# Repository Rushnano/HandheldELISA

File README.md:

# Handheld Point of Care ELISA
Electro Bio Chemical Potentiostat Testing Device for ELISA Test Cards
# 
  We are seeking contributors for creation of diversified testing device allowing consumable test cards capable of ELISA tests.

  The test cards may include protiens, enzymes, antibodies that allow capillary mixing and filtration with analyte so as to cause    a reaction in the working sensing zone. The working zone shall have excitation, sense and reference potentiostat electrodes for electronically sensing the the analyte/antibody reactions. The test card should also include near field radio frequency indentification for serial number, card test type, and date code.
  
  Added test card connections may also be included for electrophoresis as these electrodes may be required for fluidic movement. Hopefully we can limit these extra connections to the number of 8.

  The testing devices shall have circuitry and software included to perform a range of potentiostat test methods for a set of 2 electrode circuits. One set of electrodes will be sensing the real analyte response signal and the other set of electrodes will be used for relative reactions as reference. Potentiostat functions should be able to perform high resolution high sensitivity testing using static settings like many glucose meters to more complex features like differential pulse voltammetry.

  The testing device should be capable of near field radio frequency indentification reading for serial number, card test type, and date code to be used for test configuration parameters for that particular sensor card.

  App supported host connection using bluetooth should be included for intermediary cloud data services and display.

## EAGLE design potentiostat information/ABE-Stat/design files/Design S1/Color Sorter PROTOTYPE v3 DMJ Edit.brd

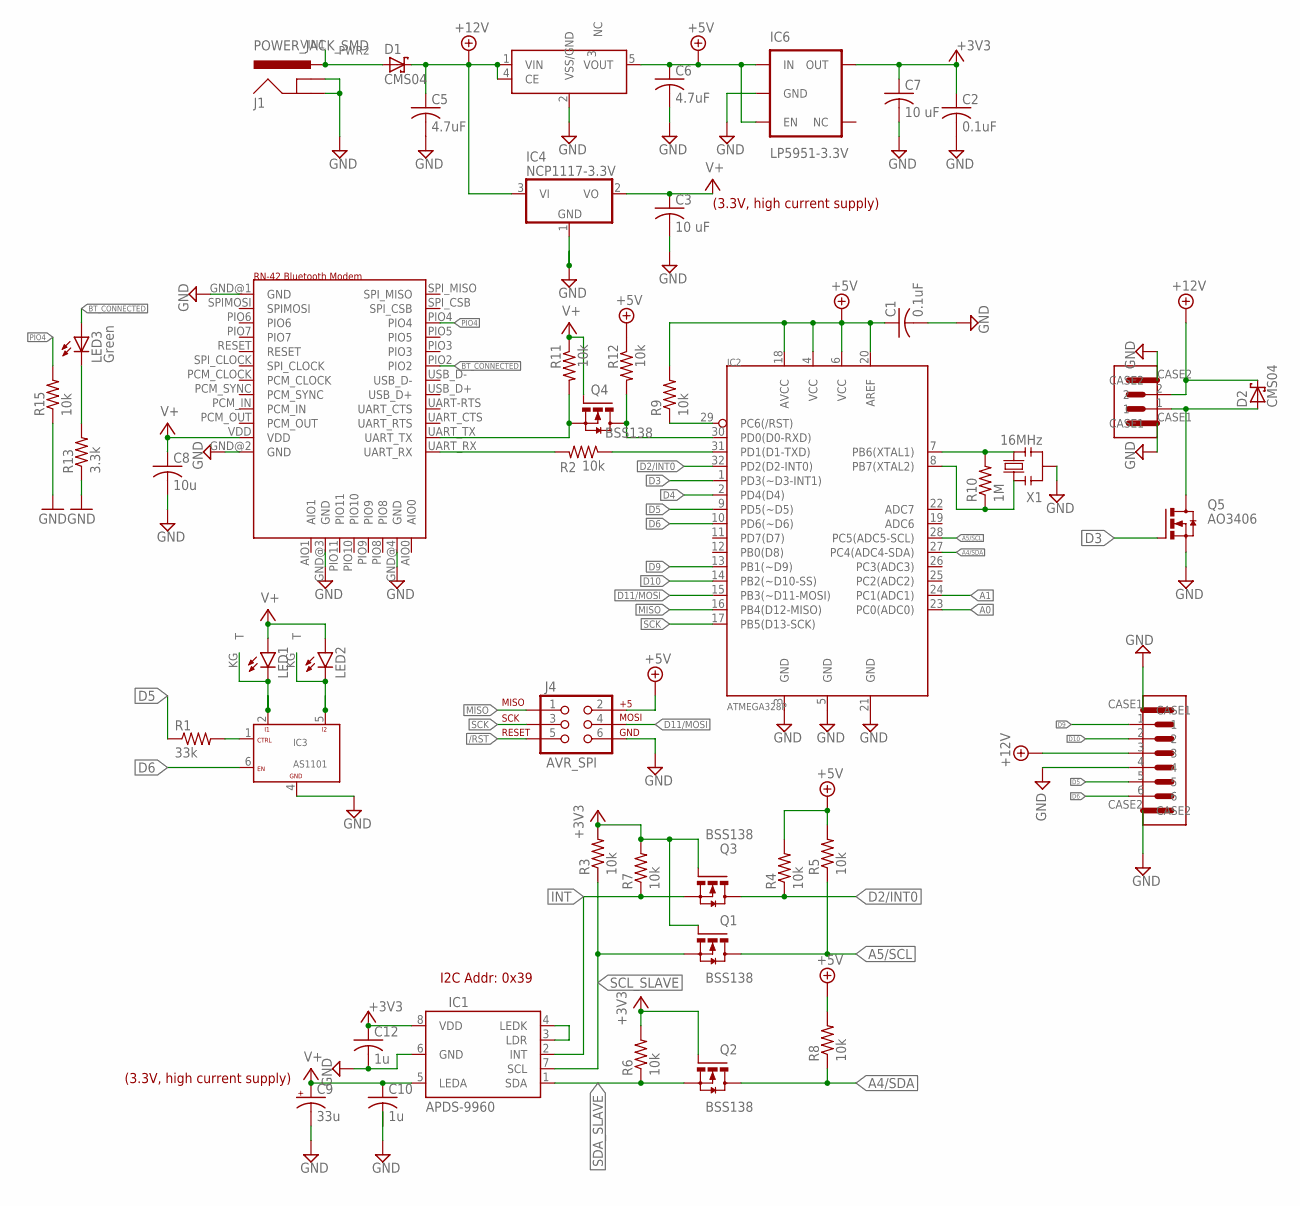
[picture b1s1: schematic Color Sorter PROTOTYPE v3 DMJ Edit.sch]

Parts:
A1: RN-42_BLUETOOTH; RN-42
C1, C2: 0.1uF; C0805
C3, C7: 10 uF; C0805
C5, C6: 4.7uF; C0805
C8: 10u; C0805
C9: 33u; CT7343
C10, C12: 1u; C0805
D1, D2: CMS04; 3-4E1A
IC1: APDS-9960; SPARKFUN-SENSORS_APDS-9960
IC2: ATMEGA328P; TQFP-32
IC3: AS1101; SC70-6
IC4: NCP1117-3.3V; SOT-223
IC5: XC6701-5V; DMJ_LINEAR_SOT23-5
IC6: LP5951-3.3V; SOT23-5
J1: POWER_JACK_SMD; SMD_POWER_JACK
J4: AVR_SPI; 2X3
LED1, LED2: LED_SAMSUNG_SPMWHT541MD7WATMS0
LED3: Green; LED-1206
Q1, Q2, Q3, Q4: BSS138; BE-420-CUSTOM-PARTS_SOT-23
Q5: AO3406; SOT-23-3
R1: 33k; R0805
R2, R3, R4, R5, R6, R7, R8, R9, R11, R12, R15: 10k; R0805
R10: 1M; R0805
R13: 3.3k; R0805
U$4: 1A-JENKINS-PHOENIX-CONTACT-CONNECTORS_1A_JENKINS_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; 1A-JENKINS-PHOENIX-CONTACT-CONNECTORS_1A_JENKINS_2013_6-PIN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
U$7: 1A_JENKINS_2013_2PIN_SMD_PHOENIX_CONTACT; 1A_JENKINS_2013_2-PIN-R/A_PHOENIX_SMD
X1: 16MHz; 1A_JENKINS_2013_RESONATOR_SMD

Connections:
+3V3: C2.1, C7.1, C12.1, IC1.8 (VDD), IC6.5 (OUT), Q1.1-G (G), Q2.1-G (G), Q3.1-G (G), R3.2, R6.2, R7.2
+5V: C1.1, C6.1, IC2.4 (VCC), IC2.6 (VCC), IC2.18 (AVCC), IC2.20 (AREF), IC5.5 (VOUT), IC6.1 (IN), IC6.3 (EN), J4.2, R4.2, R5.2, R8.2, R9.2, R12.1
+12V: C5.1, D1.C, D2.C, IC4.3 (VI), IC5.1 (VIN), IC5.4 (CE), U$4.3, U$7.2
/RST: IC2.29 (PC6(/RST)), J4.5, R9.1
A0: IC2.23 (PC0(ADC0))
A1: IC2.24 (PC1(ADC1))
A4/SDA: IC2.27 (PC4(ADC4-SDA)), Q2.3-D (D), R8.1
A5/SCL: IC2.28 (PC5(ADC5-SCL)), Q1.3-D (D), R5.1
BT_CONNECTED: A1.PIO2, LED3.A
D2/INT0: IC2.32 (PD2(D2-INT0)), Q3.3-D (D), R4.1
D3: IC2.1 (PD3(~D3-INT1)), Q5.1 (G)
D4: IC2.2 (PD4(D4))
D5: IC2.9 (PD5(~D5)), R1.1, U$4.5
D6: IC2.10 (PD6(~D6)), IC3.6 (EN), U$4.6
D9: IC2.13 (PB1(~D9)), U$4.1
D10: IC2.14 (PB2(~D10-SS)), U$4.2
D11/MOSI: IC2.15 (PB3(~D11-MOSI)), J4.4
GND: A1.GND@1 (GND), A1.GND@2 (GND), A1.GND@3 (GND), A1.GND@4 (GND), C1.2, C2.2, C3.2, C5.2, C6.2, C7.2, C8.2, C9.-, C10.2, C12.2, IC1.6 (GND), IC2.3 (GND), IC2.5 (GND), IC2.21 (GND), IC3.4 (GND), IC4.1 (GND), IC5.2 (VSS/GND), IC6.2 (GND), J1.GND, J1.P$4 (GNDBREAK), J4.6, Q5.2 (S), R13.1, R15.1, U$4.4, U$4.CASE1, U$4.CASE2, U$7.CASE1, U$7.CASE2, X1.2
INT: IC1.2 (INT), Q3.2-S (S), R7.1
MISO: IC2.16 (PB4(D12-MISO)), J4.1
unnamed: IC2.31 (PD1(D1-TXD)), R2.1
unnamed: IC1.3 (LDR), IC1.4 (LEDK)
unnamed: IC2.7 (PB6(XTAL1)), R10.2, X1.3
unnamed: IC3.2 (I1), LED1.KA (C), LED1.KG (T)
unnamed: IC3.5 (I2), LED2.KA (C), LED2.KG (T)
unnamed: A1.UART_RX, R2.2
unnamed: IC2.8 (PB7(XTAL2)), R10.1, X1.1
unnamed: D2.A, Q5.3 (D), U$7.1
unnamed: A1.UART_TX, Q4.2-S (S), R11.2
unnamed: IC2.30 (PD0(D0-RXD)), Q4.3-D (D), R12.2
unnamed: LED3.C, R13.2
unnamed: IC3.1 (CTRL), R1.2
PIO4: A1.PIO4, R15.2
SCK: IC2.17 (PB5(D13-SCK)), J4.3
SCL_SLAVE: IC1.7 (SCL), Q1.2-S (S), R3.1
SDA_SLAVE: IC1.1 (SDA), Q2.2-S (S), R6.1
USB_VIN: D1.A, J1.VIN0 (PWR), J1.VIN1 (PWR2)
V+: A1.VDD, C3.1, C8.1, C9.+, C10.1, IC1.5 (LEDA), IC4.2 (VO), LED1.A, LED2.A, Q4.1-G (G), R11.1

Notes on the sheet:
I2C Addr: 0x39
(3.3V, high current supply)

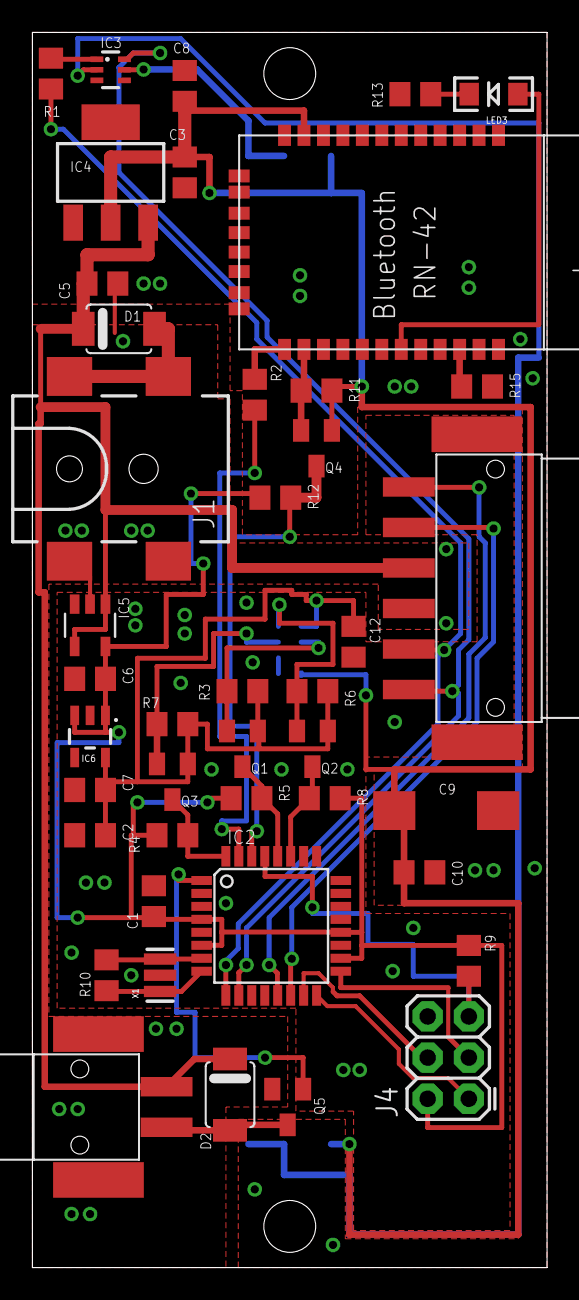
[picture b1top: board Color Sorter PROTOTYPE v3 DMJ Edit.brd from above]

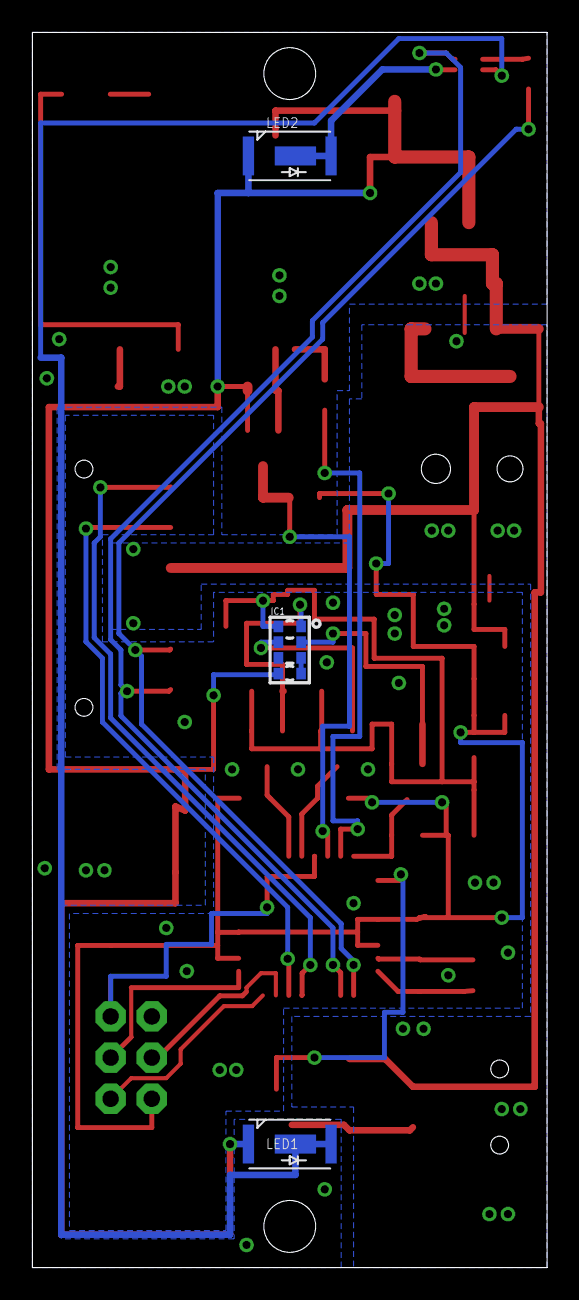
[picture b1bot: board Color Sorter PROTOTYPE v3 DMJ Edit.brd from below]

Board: 2 copper layers, 31.8 x 76.2 mm, 46 parts (3 on the bottom side), 35 nets.

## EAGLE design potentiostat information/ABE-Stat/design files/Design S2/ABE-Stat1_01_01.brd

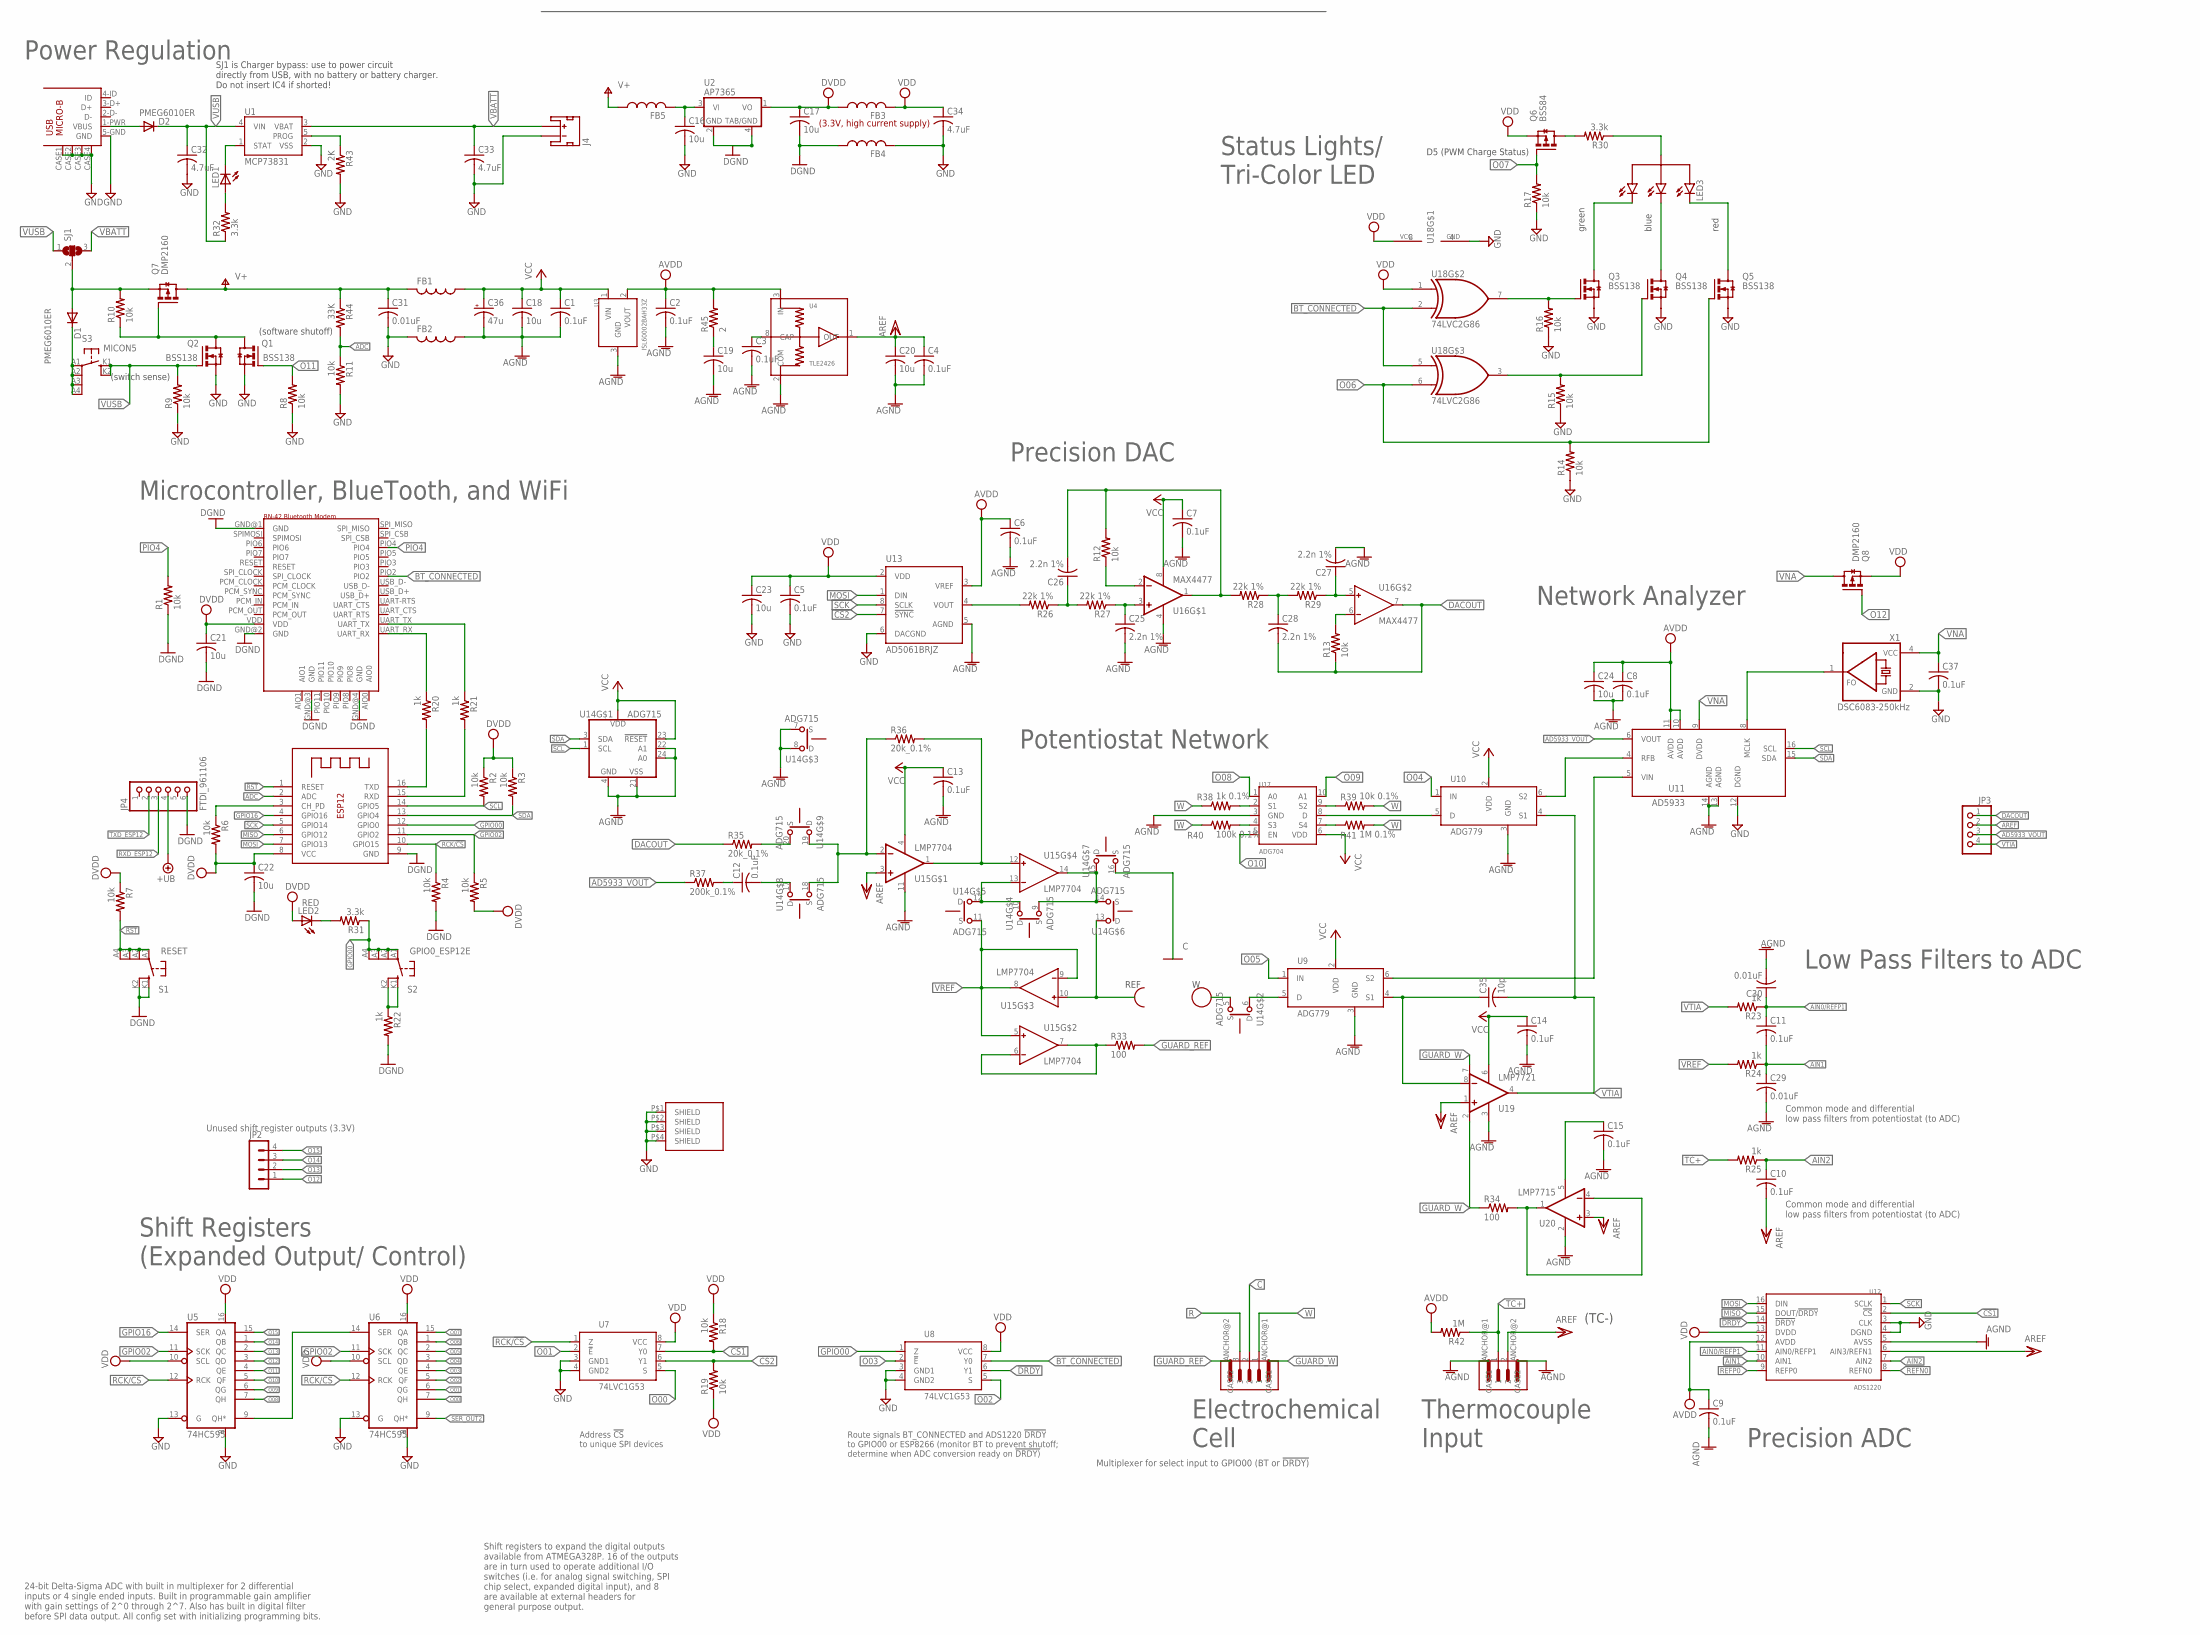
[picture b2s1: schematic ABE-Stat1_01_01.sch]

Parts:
A1: ESP-12E; ESP-12
A2: RN-42_BLUETOOTH; RN-42
C1, C2, C3, C4, C5, C6, C7, C8, C9, C10, C11, C12, C13, C14, C15, C37: 0.1uF; C0805
C16, C17, C18, C19, C20, C21, C22, C23, C24: 10u; C0805
C25, C26, C27, C28: 2.2n 1%; C0805
C29, C30, C31: 0.01uF; C0805
C32, C33, C34: 4.7uF; C0805
C35: 10p; C0805
C36: 47u; D/7343-31W
D1, D2: PMEG6010ER; DIODE_SOD123
FB1, FB2, FB3, FB4, FB5: FERRITE_BEAD_5A_0805; R0805
J1: 1A_JENKINS_2013_3PIN_SMD_PHOENIX_CONTACTVERTICAL; 3-PIN-VERT_PHOENIX_SMD
J2: 1A_JENKINS_2013_2PIN_SMD_PHOENIX_CONTACTVERTICAL; 2-PIN-VERT_PHOENIX_SMD
J3: USB-MICRO-B; USB_MICRO_B_WURTH_629105136821
J4: JST_2MM_MALE; JST-2-SMD
JP2: MA04-1
JP3: PINHD-1X4; 1X04
JP4: FTDI_961106; 6_PIN_0.1IN_STRAIGHT_HEADER
LED1: LEDCHIPLED_1206; CHIPLED_1206
LED2: RED; LED-1206
LED3: LED_RBG_COM_ANODE; LED_RGB_WURTH_150141M173100
Q1, Q2, Q3, Q4, Q5: BSS138; SOT-23
Q6: BSS84; SOT-23-3
Q7, Q8: DMP2160; SOT-23-3
R1, R2, R3, R4, R5, R6, R7, R8, R9, R10, R11, R12, R13, R14, R15, R16, R17, R18, R19: 10k; R0805
R20, R21, R22, R23, R24, R25: 1k; R0805
R26, R27, R28, R29: 22k 1%; R0805
R30, R31, R32: 3.3k; R0805
R33, R34: 100; R0805
R35, R36: 20k_0.1%; R0805
R37: 200k_0.1%; R0805
R38: 1k 0.1%; R0805
R39: 10k 0.1%; R0805
R40: 100k 0.1%; R0805
R41: 1M 0.1%; R0805
R42: 1M; R0805
R43: 2K; R0805
R44: 33K; R0805
R45: 2; R2512
S1: RESET; RAFI-MICON5_SWITCH
S2: GPIO0_ESP12E; RAFI-MICON5_SWITCH
S3: MICON5; RAFI-MICON5_SWITCH
SH1: SMARTDART_SHIELD; SMARTDART-SHIELD
SJ1: SJ2W; SJ_2
U1: MCP73831; SOT23-5
U2: AP7365; SOT-223
U3: ISL60002BAH33Z; SOT-23-3
U4: TLE2426; SOIC-8
U5, U6: 74HC595; TSSOP16
U7, U8: 74LVC1G53; VSSOP8
U9, U10: ADG779; SC70-6
U11: AD5933; SSOP-16
U12: ADS1220; TSSOP16
U13: AD5061BRJZ; SOT-23-8
U14: ADG715; TSSOP24
U15: LMP7704; TSSOP14
U16: MAX4477; UMAX8
U17: ADG704; MSOP10
U18: 74LVC2G86; US-8
U19: LMP7721; SOIC-8
U20: LMP7715; SOT23-5
X1: DSC6083-250kHz; DSC60XX_OSCILLATOR_3.2X2.5MM

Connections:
!CS1: R18.2, U7.7 (Y0), U12.2 (!CS)
!CS2: R19.2, U7.6 (Y1), U13.7 (!SYNC)
!DRDY: U8.6 (Y1), U12.14 (!DRDY)
!RST: A1.1 (RESET), R7.2, S1.A1, S1.A2 (P1), S1.A3 (P2), S1.A4 (P3)
+UB: JP4.4
AD5933_VIN: U9.6 (S2), U11.5 (VIN)
AD5933_VOUT: JP3.3, R37.1, U11.6 (VOUT)
ADC: A1.2 (ADC), R11.1, R44.2
AGND: C1.2, C2.2, C3.2, C4.2, C6.2, C7.2, C8.2, C9.2, C13.2, C14.2, C15.2, C18.2, C19.2, C20.2, C24.2, C25.2, C27.2, C29.2, C30.2, C36.-, FB2.1, J2.ANCHOR@1 (CASE1), J2.ANCHOR@2 (CASE2), U3.3 (GND), U4.2 (COM), U9.3 (GND), U10.3 (GND), U11.13 (AGND), U11.14 (AGND), U12.5 (AVSS), U13.5 (AGND), U14.4 (GND), U14.7 (S), U14.8 (D), U14.21 (VSS), U14.22 (A1), U14.24 (A0), U15.11 (V-), U16.4 (V-), U17.3 (GND), U19.3 (V-), U20.2 (V-)
AIN0/REFP1: C11.1, C30.1, R23.1, U12.11 (AIN0/REFP1)
AIN1: C11.2, C29.1, R24.1, U12.10 (AIN1)
AIN2: C10.1, R25.1, U12.7 (AIN2)
AREF: C4.1, C10.2, C20.1, J2.2, JP3.2, U4.1 (OUT), U12.6 (AIN3/REFN1), U15.3 (+IN), U19.1 (+IN), U20.3 (+IN)
AVDD: C2.1, C6.1, C8.1, C9.1, C24.1, R42.2, R45.2, U3.2 (VOUT), U4.3 (IN), U11.10 (AVDD), U11.11 (AVDD), U12.12 (AVDD), U13.3 (VREF)
BT_CONNECTED: A2.PIO2, U8.7 (Y0), U18.2 (I1), U18.5 (I0)
C: J1.2, U14.16 (S)
DACOUT: C28.2, JP3.1, R13.1, R35.1, U16.7 (OUT)
DGND: A1.9 (GND), A2.GND@1 (GND), A2.GND@2 (GND), A2.GND@3 (GND), A2.GND@4 (GND), C17.2, C21.2, C22.2, FB4.1, JP4.6, R1.1, R4.2, R22.2, S1.K1 (S), S1.K2 (S1), U2.2 (GND), U2.4 (GND1)
DVDD: A1.8 (VCC), A2.VDD, C17.1, C21.1, C22.1, FB3.1, LED2.A, R2.1, R3.1, R5.2, R6.2, R7.1, U2.1 (VO)
GND: C5.2, C16.2, C23.2, C31.2, C32.2, C33.2, C34.2, C37.2, FB2.2, FB4.2, J3.5-GND (GND), J3.CASE1 (CASE), J3.CASE2 (CASE), J3.CASE3 (CASE), J3.CASE4 (CASE), J4.1 (-), Q1.2-S (S), Q2.2-S (S), Q3.2-S (S), Q4.2-S (S), Q5.2-S (S), R8.1, R9.1, R11.2, R14.1, R15.1, R16.1, R17.1, R43.2, SH1.P$1, SH1.P$2, SH1.P$3, SH1.P$4, U1.2 (VSS), U5.8 (GND), U5.13 (G), U6.8 (GND), U6.13 (G), U7.3 (GND1), U7.4 (GND2), U8.3 (GND1), U8.4 (GND2), U11.12 (DGND), U12.3 (CLK), U12.4 (DGND), U13.6 (DACGND), U18.4 (GND), X1.2 (GND)
GPIO00: A1.12 (GPIO0), R31.1, S2.A1, S2.A2 (P1), S2.A3 (P2), S2.A4 (P3), U8.1 (Z)
GPIO02: A1.11 (GPIO2), R5.1, U5.11 (SCK), U6.11 (SCK)
GPIO16: A1.4 (GPIO16), U5.14 (SER)
GUARD_REF: J1.ANCHOR@2 (CASE2), R33.2
GUARD_W: J1.ANCHOR@1 (CASE1), R34.1, U19.2 (GUARD), U19.7 (GUARD)
MISO: A1.6 (GPIO12), U12.15 (DOUT/!DRDY)
MOSI: A1.7 (GPIO13), U12.16 (DIN), U13.1 (DIN)
unnamed: A2.UART_RX, R20.1
unnamed: U14.10 (D), U14.12 (D), U15.13 (IN-)
unnamed: D2.A, J3.1-PWR (VBUS)
unnamed: A2.UART_TX, R21.1
unnamed: Q3.1-G (G), R16.2, U18.7 (O)
unnamed: U9.5 (D), U14.6 (D)
unnamed: R43.1, U1.5 (PROG)
unnamed: U5.9 (QH*), U6.14 (SER)
unnamed: C25.1, R27.1, U16.3 (+IN)
unnamed: LED1.C, U1.1 (STAT)
unnamed: R26.2, U13.4 (VOUT)
unnamed: LED1.A, R32.2
unnamed: C19.1, R45.1
unnamed: C12.1, R37.2
unnamed: C26.1, R26.1, R27.2
unnamed: R22.1, S2.K1 (S), S2.K2 (S1)
unnamed: Q4.1-G (G), R15.2, U18.3 (O)
unnamed: D1.C, S3.A1, S3.A2 (P1), S3.A3 (P2), S3.A4 (P3)
unnamed: C3.1, U4.8 (CAP)
unnamed: C26.2, R12.2, R28.2, U16.1 (OUT)
unnamed: C28.1, R28.1, R29.2
unnamed: C27.1, R29.1, U16.5 (IN+)
unnamed: R12.1, U16.2 (-IN)
unnamed: U14.9 (S), U14.14 (S), U14.15 (D), U15.14 (OUT)
unnamed: R13.2, U16.6 (IN-)
unnamed: LED2.C, R31.2
unnamed: C12.2, U14.17 (D)
unnamed: C35.1, U9.4 (S1), U19.8 (-IN)
unnamed: R36.1, U14.18 (S), U14.19 (D), U15.2 (-IN)
unnamed: R36.2, U15.1 (OUT), U15.12 (IN+)
unnamed: U10.6 (S2), U11.4 (RFB)
unnamed: R41.1, U17.7 (S4)
unnamed: R33.1, U15.6 (IN-), U15.7 (OUT)
unnamed: R39.1, U17.9 (S2)
unnamed: Q1.3-D (D), Q2.3-D (D), Q7.1 (G), R10.1
unnamed: U10.5 (D), U17.8 (D)
unnamed: R38.2, U17.2 (S1)
unnamed: R40.2, U17.4 (S3)
unnamed: LED3.G, Q3.3-D (D)
unnamed: R34.2, U20.1 (OUT), U20.4 (-IN)
unnamed: LED3.B, Q4.3-D (D)
unnamed: LED3.R, Q5.3-D (D)
unnamed: Q6.3 (D), R30.2
unnamed: LED3.A, R30.1
unnamed: R35.2, U14.20 (S)
unnamed: C16.1, FB5.2, U2.3 (VI)
unnamed: A1.3 (CH_PD), R6.1
unnamed: U11.8 (MCLK), X1.1 (FO)
unnamed: D1.A, Q7.2 (S), R10.2, SJ1.2
O00: U6.7 (QH), U7.5 (S)
O01: U6.6 (QG), U7.2 (!E)
O02: U6.5 (QF), U8.5 (S)
O03: U6.4 (QE), U8.2 (!E)
O04: U6.3 (QD), U10.1 (IN)
O05: U6.2 (QC), U9.1 (IN)
O06: Q5.1-G (G), R14.2, U6.1 (QB), U18.6 (I1)
O07: Q6.1 (G), R17.2, U6.15 (QA)
O08: U5.7 (QH), U17.1 (A0)
O09: U5.6 (QG), U17.10 (A1)
O10: U5.5 (QF), U17.5 (EN)
O11: Q1.1-G (G), R8.2, U5.4 (QE)
O12: JP2.1, Q8.1 (G), U5.3 (QD)
O13: JP2.2, U5.2 (QC)
O14: JP2.3, U5.1 (QB)
O15: JP2.4, U5.15 (QA)
PIO4: A2.PIO4, R1.2
R: J1.3, U14.13 (D), U15.10 (IN+)
RCK/!CS: A1.10 (GPIO15), R4.1, U5.12 (RCK), U6.12 (RCK), U7.1 (Z)
REFN0: U12.8 (REFN0)
REFP0: U12.9 (REFP0)
RXD_ESP12: A1.15 (RXD), JP4.3, R21.2
SCK: A1.5 (GPIO14), U12.1 (SCLK), U13.8 (SCLK)
SCL: A1.14 (GPIO5), R2.2, U11.16 (SCL), U14.1 (SCL)
SDA: A1.13 (GPIO4), R3.2, U11.15 (SDA), U14.3 (SDA)
SER_OUT2: U6.9 (QH*)
TC+: J2.1, R25.2, R42.1
TXD_ESP12: A1.16 (TXD), JP4.2, R20.2
V+: C31.1, FB1.2, FB5.1, Q7.3 (D), R44.1
VBATT: C33.1, J4.2 (+), SJ1.3, U1.3 (VBAT)
VCC: C1.1, C7.1, C13.1, C14.1, C15.1, C18.1, C36.+, FB1.1, U3.1 (VIN), U9.2 (VDD), U10.2 (VDD), U14.2 (VDD), U14.23 (!RESET), U15.4 (V+), U16.8 (V+), U17.6 (VDD), U19.6 (V+), U20.5 (V+)
VDD: C5.1, C23.1, C34.1, FB3.2, Q6.2 (S), Q8.2 (S), R18.1, R19.1, U5.10 (SCL), U5.16 (VCC), U6.10 (SCL), U6.16 (VCC), U7.8 (VCC), U8.8 (VCC), U12.13 (DVDD), U13.2 (VDD), U18.1 (I0), U18.8 (VCC)
VNA: C37.1, Q8.3 (D), U11.9 (DVDD), X1.4 (VCC)
VREF: R24.2, U14.11 (S), U15.5 (IN+), U15.8 (OUT), U15.9 (IN-)
VTIA: C35.2, JP3.4, R23.2, U10.4 (S1), U19.4 (OUT)
VUSB: C32.1, D2.C, Q2.1-G (G), R9.2, R32.1, S3.K1 (S), S3.K2 (S1), SJ1.1, U1.4 (VIN)
W: J1.1, R38.1, R39.2, R40.1, R41.2, U14.5 (S)

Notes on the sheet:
(3.3V, high current supply)
Route signals BT_CONNECTED and ADS1220 !DRDY to GPIO00 or ESP8266 (monitor BT to prevent shutoff; determine when ADC conversion ready on !DRDY)
Shift registers to expand the digital outputs available from ATMEGA328P. 16 of the outputs are in turn used to operate additional I/O switches (i.e. for analog signal switching, SPI chip select, expanded digital input), and 8 are available at external headers for general purpose output.
Multiplexer for select input to GPIO00 (BT or !DRDY)
Power Regulation
Microcontroller, BlueTooth, and WiFi
Precision ADC
Shift Registers (Expanded Output/ Control)
24-bit Delta-Sigma ADC with built in multiplexer for 2 differential inputs or 4 single ended inputs. Built in programmable gain amplifier with gain settings of 2^0 through 2^7. Also has built in digital filter before SPI data output. All config set with initializing programming bits.
Common mode and differential low pass filters from potentiostat (to ADC)
Address !CS to unique SPI devices
(switch sense)
(software shutoff)
Precision DAC
Network Analyzer
Potentiostat Network
Low Pass Filters to ADC
Thermocouple Input
Electrochemical Cell
D5 (PWM Charge Status)
green
blue
red
Status Lights/ Tri-Color LED
(TC-)
Unused shift register outputs (3.3V)
REF
SJ1 is Charger bypass: use to power circuit directly from USB, with no battery or battery charger. Do not insert IC4 if shorted!

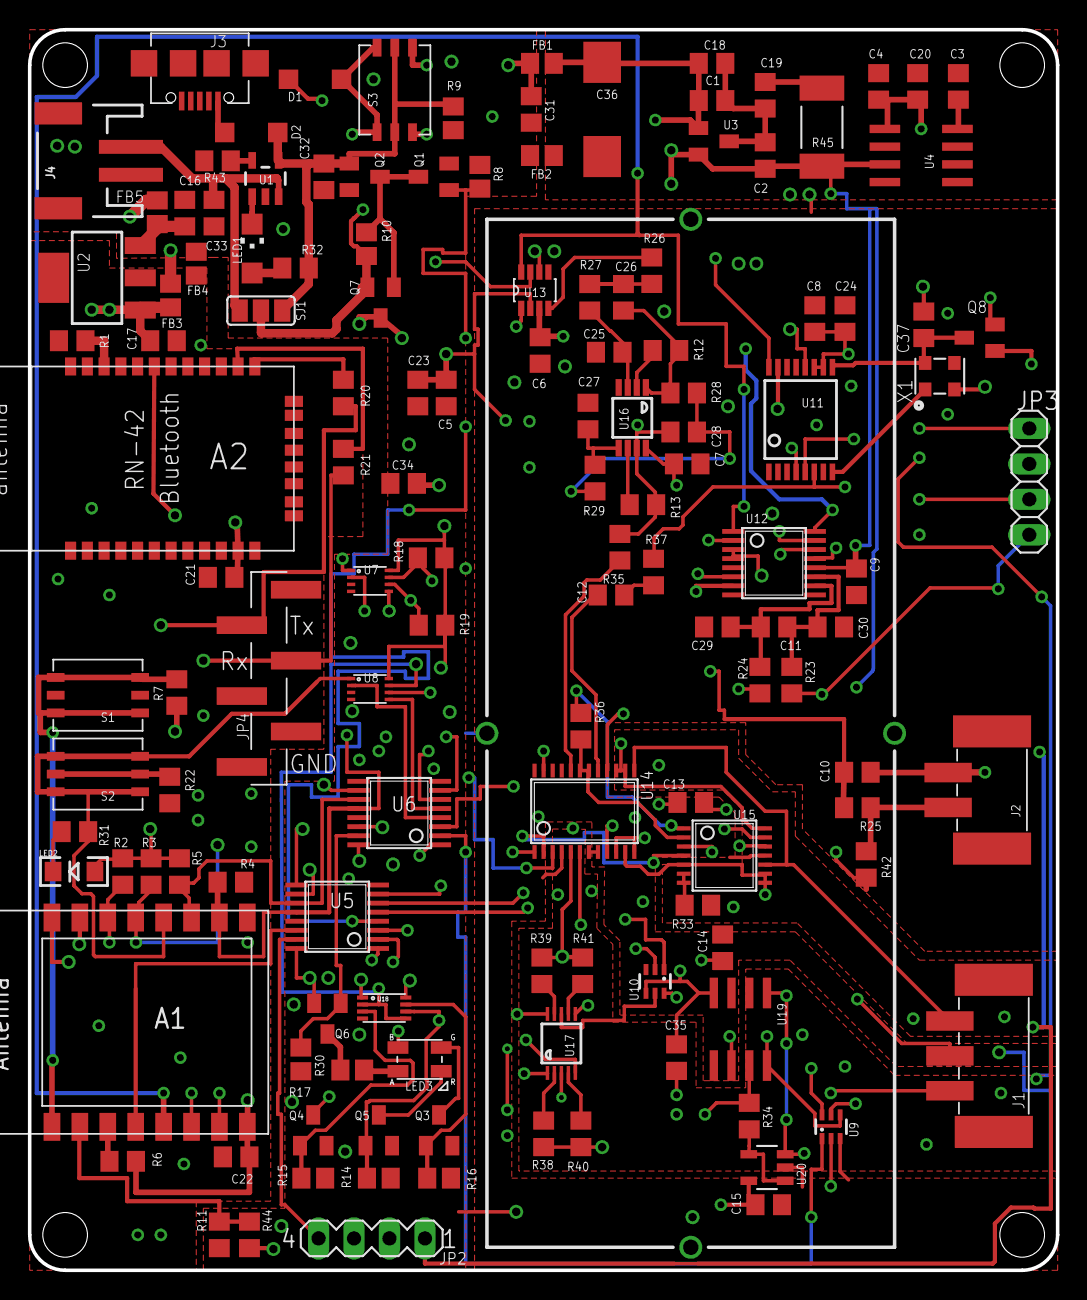
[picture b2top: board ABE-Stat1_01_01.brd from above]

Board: 4 copper layers, 73.7 x 88.9 mm, 135 parts (0 on the bottom side), 109 nets.

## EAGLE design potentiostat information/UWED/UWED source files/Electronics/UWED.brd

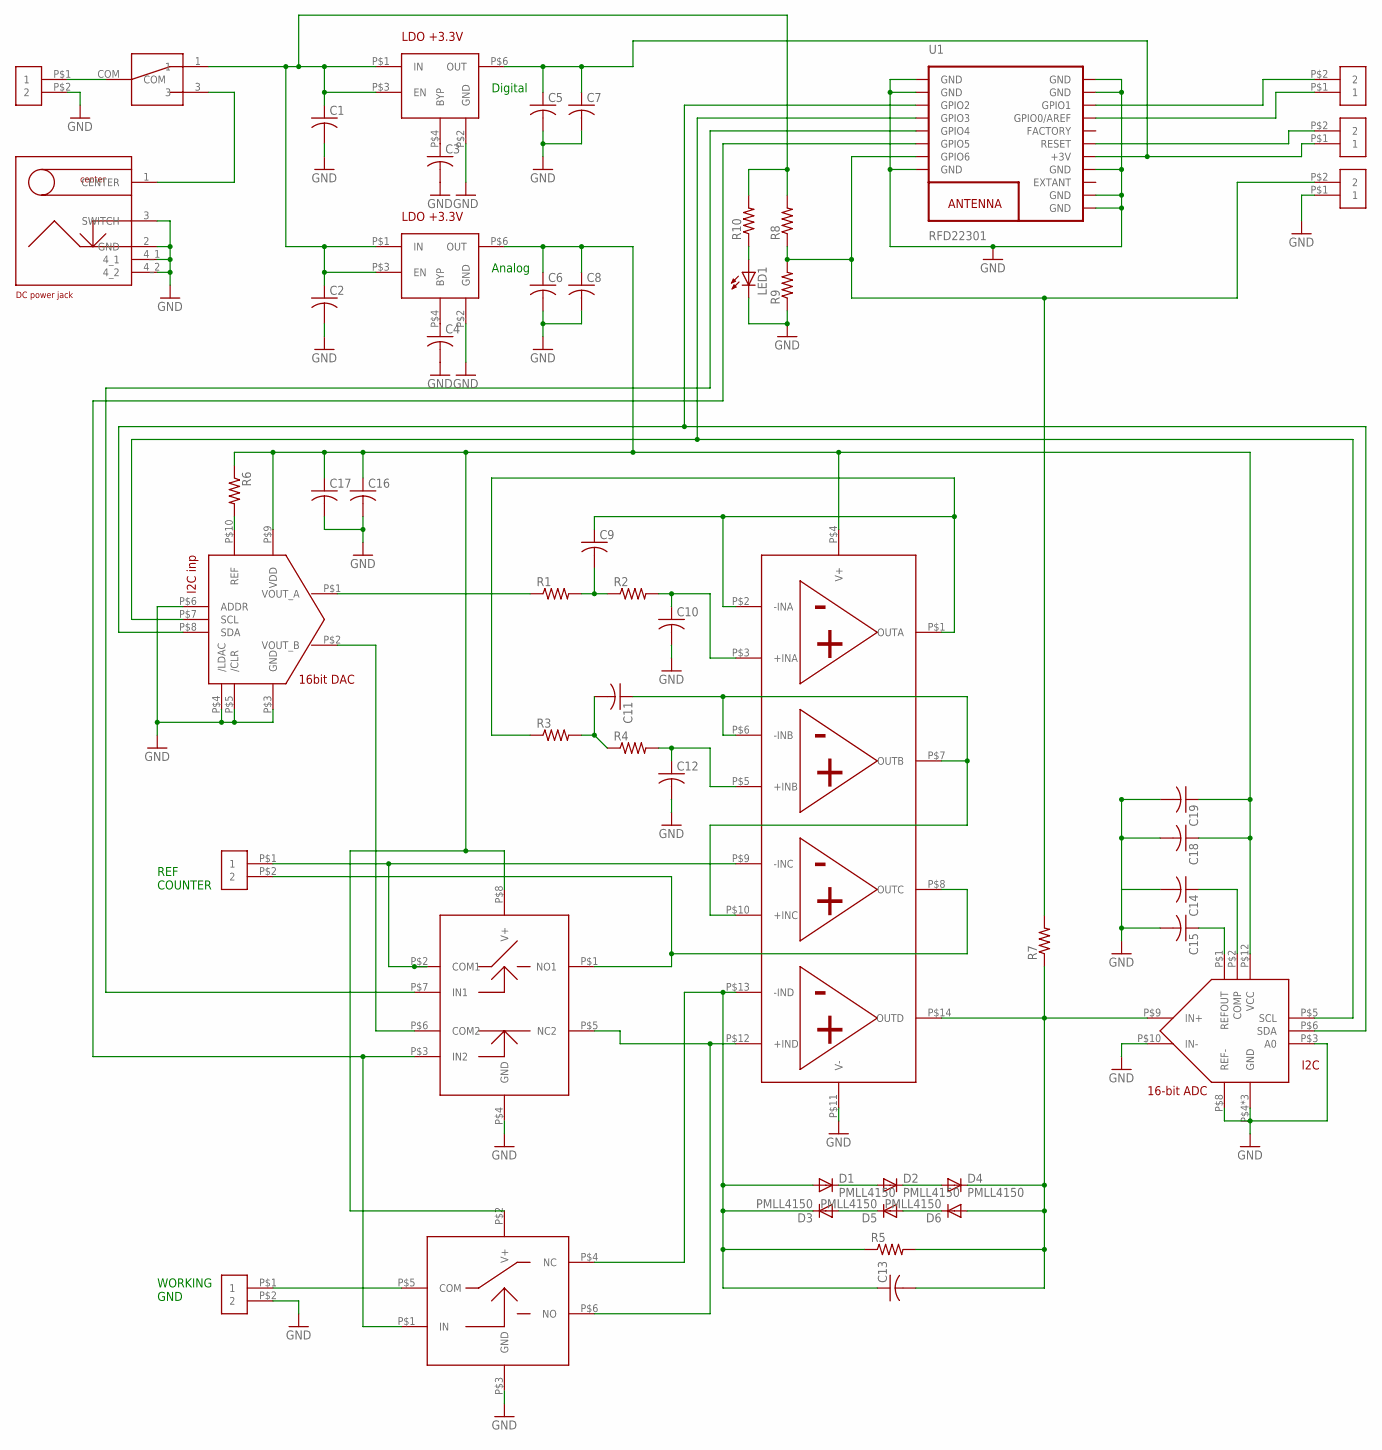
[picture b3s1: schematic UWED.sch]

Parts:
C1, C2, C3, C4, C5, C6, C7, C8, C9, C10, C11, C12, C13, C14, C15, C16, C17, C18, C19: C-USC0805; C0805
D1, D2, D3, D4, D5, D6: PMLL4150; SOD80C
LED1: LEDSML0805; SML0805
R1, R2, R3, R4, R5, R6, R7, R8, R9, R10: R-US_R0805; R0805
U1: RFD22301
U$1: 4OPAMPS-AD8608ARUZ; MSOP14_0.65MM
U$2: ADC_LTC2471IMS; MSOP12_0.65MM
U$3, U$4, U$5, U$6, U$7, U$15: CONTACT_PADS_SMD_2
U$8: DAC_AD5667RBRMZ-2; MSOP10_0.5MM
U$9: DC_JACK_0.7MM; PJ-032H-SMT
U$10, U$11: LDO-MIC5205-3.3YM5-TR; SOT-23-6
U$12: SWITCH_MAX4643EUA; MSOP8_0.65MM
U$13: SWITCH_MAX4644EUT; SOT-23-6
U$14: SW_TOGGLELARGE; TOGGLE_34E

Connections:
GND: C1.2, C2.2, C3.2, C4.2, C5.2, C6.2, C7.2, C8.2, C10.2, C12.2, C14.2, C15.2, C16.2, C17.2, C18.2, C19.2, LED1.C, R9.1, U1.1 (GND), U1.2 (GND), U1.8 (GND), U1.9 (GND), U1.10 (GND), U1.12 (GND), U1.18 (GND), U1.19 (GND), U$1.P$11 (V-), U$2.P$3 (A0), U$2.P$4 (GND), U$2.P$7 (GND), U$2.P$8 (REF-), U$2.P$10 (IN-), U$2.P$11 (GND), U$3.P$2 (2), U$6.P$2 (2), U$8.P$3 (GND), U$8.P$4 (/LDAC), U$8.P$5 (/CLR), U$8.P$6 (ADDR), U$9.2 (GND), U$9.3 (SWITCH), U$9.4_1, U$9.4_2, U$10.P$2 (GND), U$11.P$2 (GND), U$12.P$4 (GND), U$13.P$3 (GND), U$15.P$1 (1)
unnamed: U$3.P$1 (1), U$14.COM
unnamed: U$9.1 (CENTER), U$14.3
unnamed: C1.1, C2.1, R8.2, R10.2, U$10.P$1 (IN), U$10.P$3 (EN), U$11.P$1 (IN), U$11.P$3 (EN), U$14.1
unnamed: C3.1, U$10.P$4 (BYP)
unnamed: C4.1, U$11.P$4 (BYP)
unnamed: C6.1, C8.1, C16.1, C17.1, C18.1, C19.1, R6.1, U$1.P$4 (V+), U$2.P$12 (VCC), U$8.P$9 (VDD), U$11.P$6 (OUT), U$12.P$8 (V+), U$13.P$2 (V+)
unnamed: C5.1, C7.1, U1.13 (+3V), U$4.P$1 (1), U$10.P$6 (OUT)
unnamed: C9.1, R3.1, U$1.P$1 (OUTA), U$1.P$2 (-INA)
unnamed: R1.1, U$8.P$1 (VOUT_A)
unnamed: C9.2, R1.2, R2.1
unnamed: U$1.P$8 (OUTC), U$7.P$2 (2), U$12.P$1 (NO1)
unnamed: C10.1, R2.2, U$1.P$3 (+INA)
unnamed: C11.1, U$1.P$6 (-INB), U$1.P$7 (OUTB), U$1.P$10 (+INC)
unnamed: C11.2, R3.2, R4.1
unnamed: C12.1, R4.2, U$1.P$5 (+INB)
unnamed: U$1.P$9 (-INC), U$7.P$1 (1), U$12.P$2 (COM1)
unnamed: U$6.P$1 (1), U$13.P$5 (COM)
unnamed: C13.1, D1.A, D3.C, R5.1, U$1.P$13 (-IND), U$13.P$4 (NC)
unnamed: U$1.P$12 (+IND), U$12.P$5 (NC2), U$13.P$6 (NO)
unnamed: U1.6 (GPIO5), U$12.P$3 (IN2), U$13.P$1 (IN)
unnamed: C13.2, D4.C, D6.A, R5.2, R7.1, U$1.P$14 (OUTD), U$2.P$9 (IN+)
unnamed: D5.A, D6.C
unnamed: D3.A, D5.C
unnamed: D2.C, D4.A
unnamed: D1.C, D2.A
unnamed: U$8.P$2 (VOUT_B), U$12.P$6 (COM2)
unnamed: U1.3 (GPIO2), U$2.P$6 (SDA), U$8.P$8 (SDA)
unnamed: C15.1, U$2.P$1 (REFOUT)
unnamed: C14.1, U$2.P$2 (COMP)
unnamed: R6.2, U$8.P$10 (REF)
unnamed: U1.4 (GPIO3), U$2.P$5 (SCL), U$8.P$7 (SCL)
unnamed: U1.17 (GPIO1), U$5.P$2 (2)
unnamed: U1.16 (GPIO0/AREF), U$5.P$1 (1)
unnamed: U1.14 (RESET), U$4.P$2 (2)
unnamed: U1.5 (GPIO4), U$12.P$7 (IN1)
unnamed: R7.2, R8.1, R9.2, U1.7 (GPIO6), U$15.P$2 (2)
unnamed: LED1.A, R10.1

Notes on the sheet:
Digital
Analog
REF COUNTER
WORKING GND

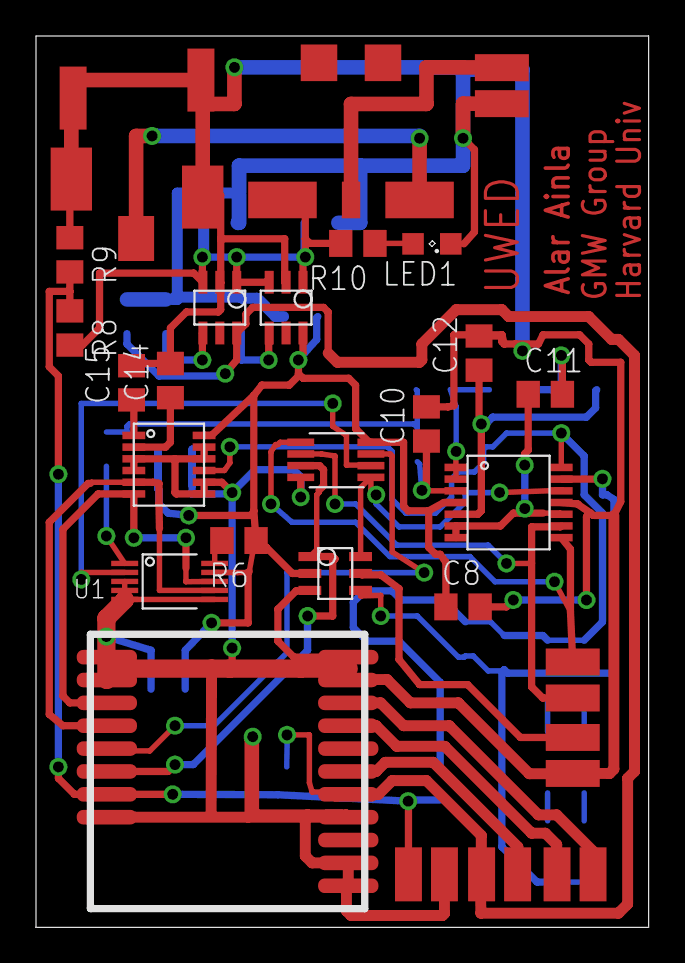
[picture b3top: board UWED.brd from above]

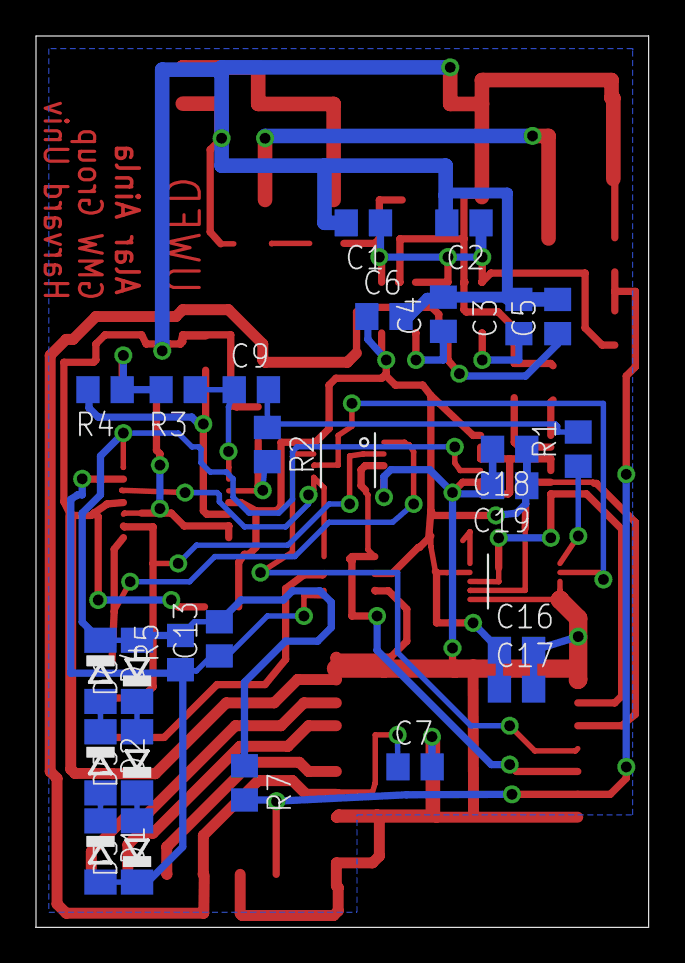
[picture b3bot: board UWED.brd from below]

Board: 2 copper layers, 34.0 x 49.5 mm, 52 parts (25 on the bottom side), 38 nets.

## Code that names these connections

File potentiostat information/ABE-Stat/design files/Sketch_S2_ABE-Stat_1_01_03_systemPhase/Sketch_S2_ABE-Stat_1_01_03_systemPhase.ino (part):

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  Updated March 23, 2017- largely to address hardware design changes on new design iteration NC1194 Potentiostat V3. These include use of i2c octal switch ADG715 for 
  potentiostat signal switching (A0 and A1 on ADG715 pulled to ground, so i2c address is 0x48). Network analyzer AD5933 address is 0x0D. Other changes are use of 
  low dropout 3.3V regulator AP7365 for wireless devices (high side switching transistor of TPS 62172was not able to deliver required current from single cell Lithium battery),
  corrected i2c pinout for ESP8266 (GPIO5 for SCL, GPIO4 for SDA), and reconfigured potentiostat network (error made in earlier designs).

  Updated dates up to about April 24, 2017- include code to read and communicate temperature, and impedance register values from AD5933 for given frequency, as well as
  current and voltage applied through transimpedance amplifier...
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  Shift register outputs (2x serialized 74HC595, O00 - O15):
      O00 74LVG1G53 switch1 signal (!CS to !CS1 (ADS1220/ "0") or !CS2 (AD5061/ "1")
      O01 74LVG1G53 switch1 !enable (!CS1 && !CS2 pulled high if O01 high)
      O02 74LVG1G53 switch2 signal (RN42 BT_Connected "0" or ADS1220 !DRDY "1" to GPIO00)
      O03 74LVG1G53 switch2 !enable (GPIO00 floats when O03 high)
      O04 ADG779 switch1 signal (TIA feedback to LMP7721 Vout "0" or AD59933 RFB "1")
      O05 ADG779 switch2 signal (TIA input to LMP7721 V- "0" or AD5933 Vin "1")
      O06 Input to illuminate red segment of 3-color LED
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
// i2c and SPI default pins based on definitions using the pinout shown at https://github.com/esp8266/Arduino/blob/master/doc/reference.md 

// GPIO00 assigned as input (listen for either !DRDY from ADS1220, or BluetoothConnected Signal)
#define GPIO00            0

// map to connect ESP8266 !CS to corresponding !CS pins on ADS1220 or AD5061 (only allow one to connect at a time, other is always pulled high- make sure that both
// devices are not writing to MISO simultaneously (even though AD5061 doesn't have a data out pin)
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  pinMode(CS_RCK, OUTPUT); // also used as CS for SPI
  pinMode(CLOCK, OUTPUT);

  pinMode(0, INPUT);  // GPIO 00 is input (used to measure BT connected or ADS1220 !DRDY signals

  // SPI pins
  pinMode(MOSI, OUTPUT);
  pinMode(MISO, INPUT);
  pinMode(SCK, OUTPUT);

  pinMode(GPIO00, INPUT);

  devicePower(true);  // activate digital pin to supply power from battery

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
  //openCircuitConfig();  // here we are testing open circuit configuration to measure open circuit voltage; must be < 2.048 V...
                          
  Release_GPIO00(); // don't connect GPIO00 to !DRDY or BT_Connected (allow user a time to reset ESP8266 into programming mode)

  illuminateLED();  // make sure power is supplied to tri-color LED
  redLED(true); // then turn on red LED of tri-color initially just to make sure it works

  delay(500);  // use a software delay function here to enable program to be reset to reprogram mode
      //- now we're changing the code to generate a sin wave as fast as possible, but still only measure the thermocouple voltage periodically (so removing delays from main loop- won't get another opportunity to keep GPIO00 released)
  
  
  redLED(false);  // then turn LED back off (should go back to green, unless bluetooth is connected which is highly unlikely at startup)
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
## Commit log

2020-03-25 Create test
2020-03-25 Update and rename readme.md to pcbNotes
2020-03-25 Create notes
2020-03-27 Create host software
2020-03-27 Rename Dr. Plaxco video link.txt to Dr. Plaxco video link.md

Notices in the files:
parts and their libraries:
SparkFun-Connectors: Licensing: Creative Commons ShareAlike 4.0 International - https://creativecommons.org/licenses/by-sa/4.0
